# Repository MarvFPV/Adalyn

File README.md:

# Adalyn
36key QAZ-like handwired keyboard based on the great idea by somepin here on GitHub, check out his repo [here](https://github.com/somepin/qal-handwire)

Handwires of the keyboard are confirmed working, although we also have someone working on a PCB. 
Currently, the top and bottom are pretty much a friction fit, be aware of that when printing / ordering this case from a fab.

## Required components for handwires
(For building a handwired Adalyn please use the 3D files from the handwire branch)

* 36 MX style switches
* 2 2u MX platemount stabs
* 36 Diodes
* a Promicro
* one of ai03's [unified daughterboards](https://github.com/ai03-2725/Unified-Daughterboard)
* a few cables to wire up the matrix
* 4 m3x6mm screws
* 4 m3x8mm countersunk screws

I personally tend to remove the microUSB connector from the Promicro and solder it directly to a unified daughterboard, that's also why the Promicro cutout may not fit with the USB connector still on the PCB. (I should really write up some documentation on that ^^)

## PCB version
The adjusted Case files for the PCB version are currently not on this repo, they will be added later down the line.

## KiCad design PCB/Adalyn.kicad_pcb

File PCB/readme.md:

# Adalyn PCB
After the development of the handwired Adalyn case, it was clear this great combination needed a formalized pcb. This is that PCB. Designed by tominabox1, the pcb features an ATmega32u4a, USB-C, and ESD protection. The pcb is supported in QMK and VIAL. 

# BOM
The bill of materials is listed below, with LCSC parts where possible. Total unique part count: 14. Total parts: 37. 

| Ref                                                                                                        | Qnty | Value              | Part     | Footprint                                                          |
|------------------------------------------------------------------------------------------------------------|------|--------------------|----------|--------------------------------------------------------------------|
| C1, C2, C4, C101                                                                                           | 4    | 100nF              | C187860  | 0603                                                               |
| C5                                                                                                         | 1    | 10uF               | C97885   | 0603                                                               |
| C6                                                                                                         | 1    | 1uF                | C302042  | 0603                                                               |
| D101, D102, D103, D104, D105, D106, D107, D108, D109, D110, D111, D112, D113, D114, D115, D116, D117, D118 | 18   | BAV70              | C181110  | SOT-23                                                             |
| F101                                                                                                       | 1    | 700mA              | C182438  | 0603                                                               |
| L101                                                                                                       | 1    | 600R@100MHz        | C139183  | 0603                                                               |
| R2, R3                                                                                                     | 2    | 22                 | C96423   | 0603                                                               |
| R4, R5                                                                                                     | 2    | 10k                | C73809   | 0603                                                               |
| R101, R102                                                                                                 | 2    | 5.1k               | C415096  | 0603                                                               |
| SW1                                                                                                        | 1    | SW_Push            | C589220  | 4.9x4.9                                                            |
| U101                                                                                                       | 1    | ATmega32U4-A       | C44854   | TQFP-44_10x10mm_P0.8mm                                             |
| U102                                                                                                       | 1    | PRTR5V0U2X         | C2827688 | SOT-143                                                            |
| USB101                                                                                                     | 1    | HRO-TYPE-C-31-M-12 | C165948  | HRO-TYPE-C-31-M-12                                                 |
| Y1                                                                                                         | 1    | 16MHz              | C341521  | Crystal:Resonator_SMD_Murata_CSTxExxV-3Pin_3.0x1.1mm_HandSoldering |

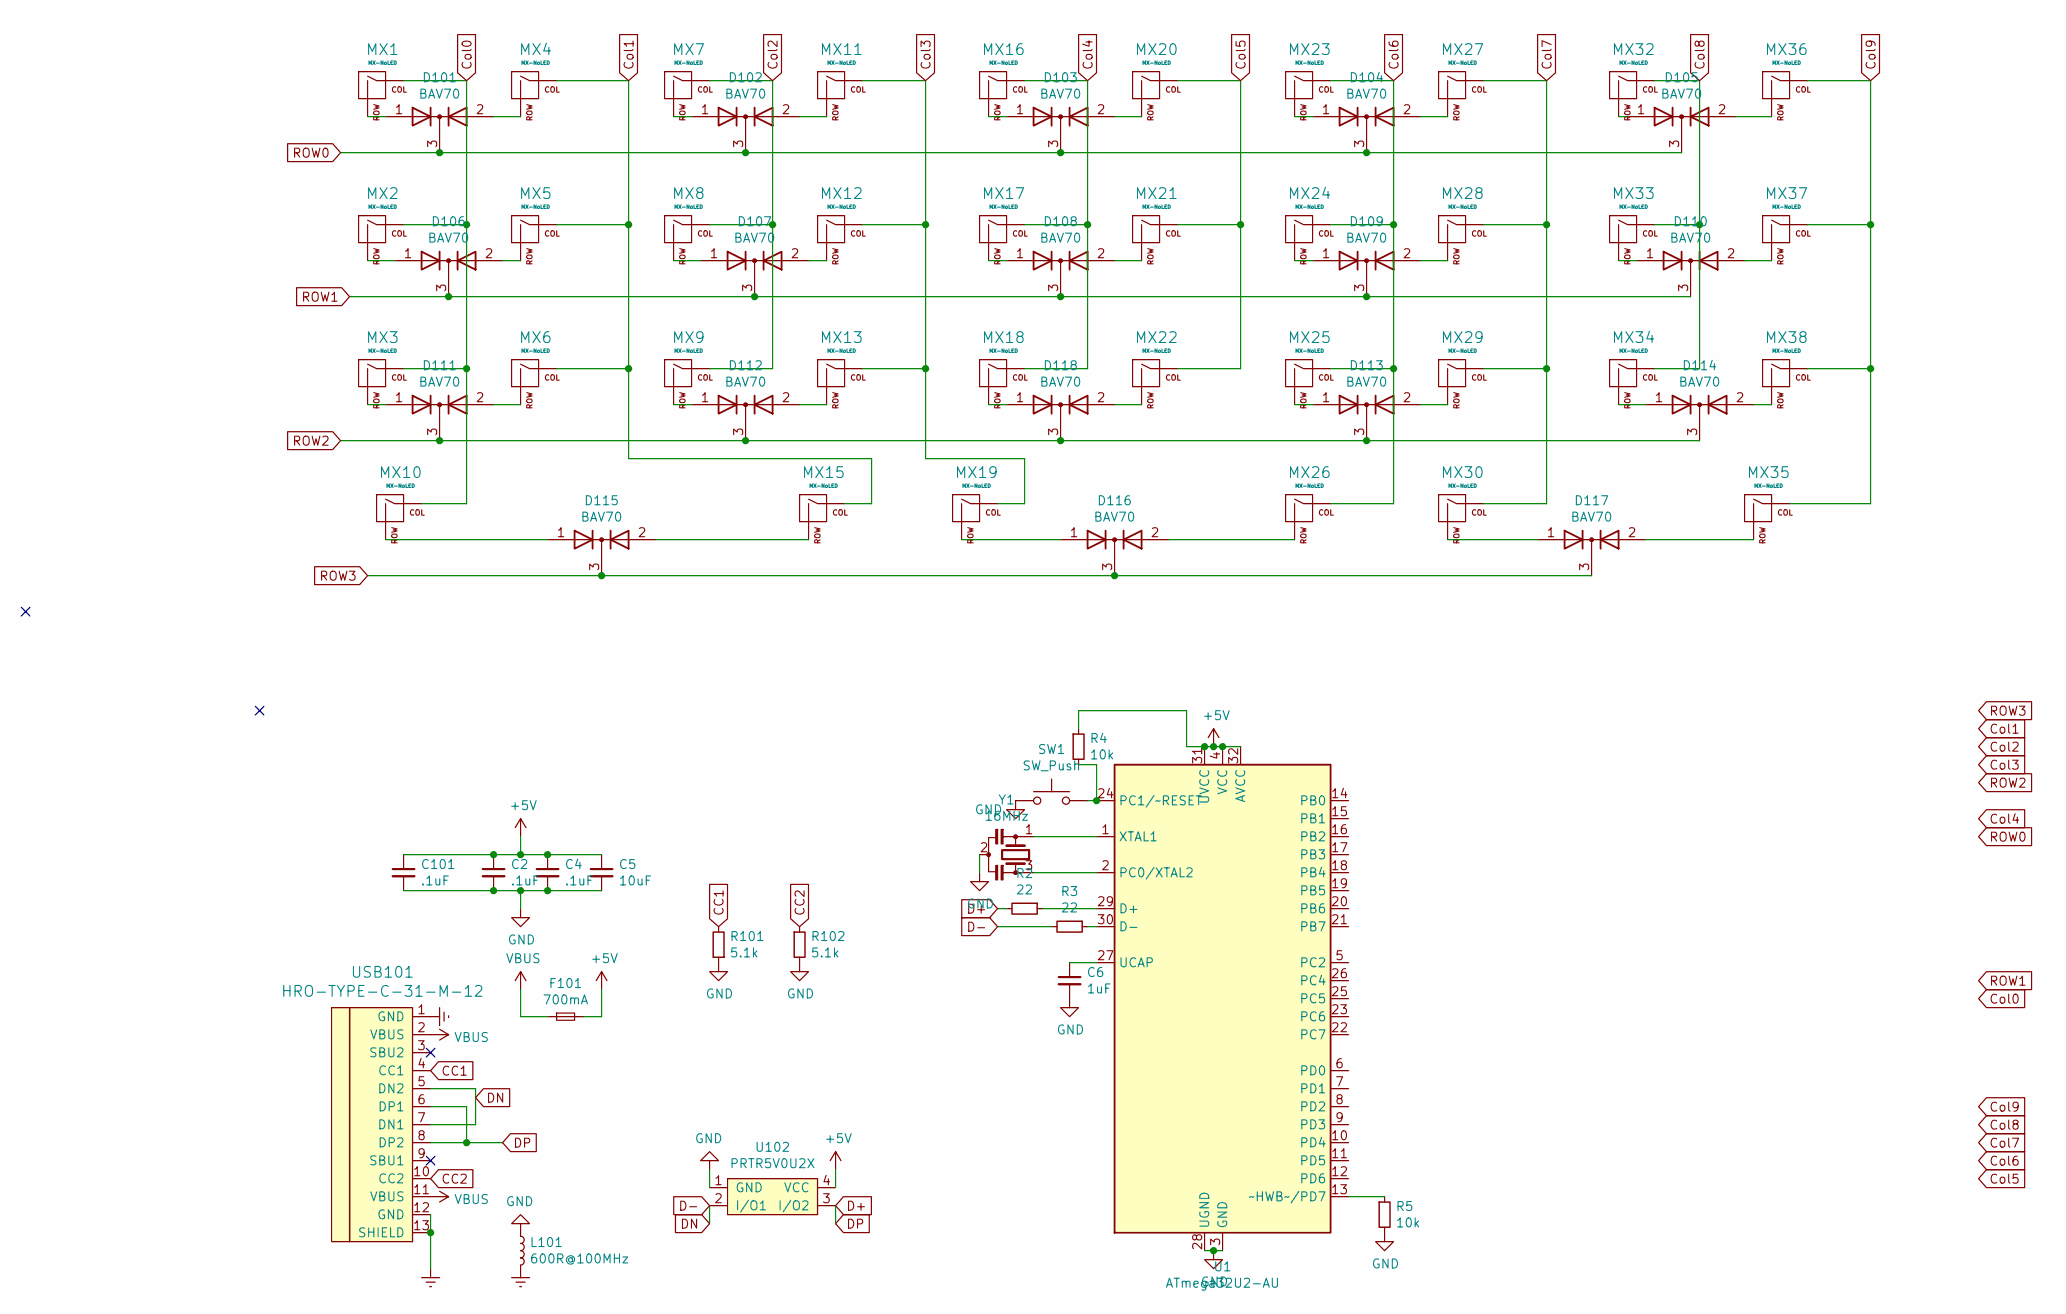
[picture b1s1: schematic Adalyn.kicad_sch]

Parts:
C2, C4, C101: .1uF; C_0603_1608Metric_Pad1.08x0.95mm_HandSolder
C5: 10uF; C_0603_1608Metric_Pad1.08x0.95mm_HandSolder
C6: 1uF; C_0603_1608Metric_Pad1.08x0.95mm_HandSolder
D101, D102, D103, D104, D105, D106, D107, D108, D109, D110, D111, D112, D113, D114, D115, D116, D117, D118: BAV70; SOT-23
F101: 700mA; Fuse_0603_1608Metric
L101: 600R@100MHz; L_0603_1608Metric
MX1, MX2, MX3, MX4, MX5, MX6, MX7, MX8, MX9, MX10, MX11, MX12, MX13, MX15, MX16, MX17, MX18, MX19, MX20, MX21, MX22, MX23, MX24, MX25, MX26, MX27, MX28, MX29, MX30, MX32, MX33, MX34, MX35, MX36, MX37, MX38: MX-NoLED; MXOnly-1U-NoLED
R2, R3: 22; R_0603_1608Metric_Pad0.98x0.95mm_HandSolder
R4, R5: 10k; R_0603_1608Metric_Pad0.98x0.95mm_HandSolder
R101, R102: 5.1k; R_0603_1608Metric
SW1: SW_Push; SW_SPST_TL3342
U1: ATmega32U2-AU; TQFP-32_7x7mm_P0.8mm
U102: PRTR5V0U2X; SOT-143
USB101: HRO-TYPE-C-31-M-12; HRO-TYPE-C-31-M-12-Assembly
Y1: 16MHz; Resonator_SMD_muRata_CSTxExxV-3Pin_3.0x1.1mm

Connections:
+5V: C2.1, C4.1, C5.1, C101.1, F101.2, R4.1, U1.4 (VCC), U1.31 (UVCC), U1.32 (AVCC), U102.4 (VCC)
CC1: R101.2, USB101.4 (CC1)
CC2: R102.1, USB101.10 (CC2)
Col0: MX1.1 (COL), MX2.1 (COL), MX3.1 (COL), MX10.1 (COL)
Col1: MX4.1 (COL), MX5.1 (COL), MX6.1 (COL), MX15.1 (COL)
Col2: MX7.1 (COL), MX8.1 (COL), MX9.1 (COL)
Col3: MX11.1 (COL), MX12.1 (COL), MX13.1 (COL), MX19.1 (COL)
Col4: MX16.1 (COL), MX17.1 (COL), MX18.1 (COL)
Col5: MX20.1 (COL), MX21.1 (COL), MX22.1 (COL)
Col6: MX23.1 (COL), MX24.1 (COL), MX25.1 (COL), MX26.1 (COL)
Col7: MX27.1 (COL), MX28.1 (COL), MX29.1 (COL), MX30.1 (COL)
Col8: MX32.1 (COL), MX33.1 (COL), MX34.1 (COL)
Col9: MX35.1 (COL), MX36.1 (COL), MX37.1 (COL), MX38.1 (COL)
D+: R2.2, U102.3 (I/O2), USB101.6 (DP1), USB101.8 (DP2)
D-: R3.2, U102.2 (I/O1), USB101.5 (DN2), USB101.7 (DN1)
Earth: L101.2, USB101.1 (GND), USB101.12 (GND), USB101.13 (SHIELD)
GND: C2.2, C4.2, C5.2, C6.2, C101.2, L101.1, R5.2, R101.1, R102.2, SW1.1, U1.3 (GND), U1.28 (UGND), U102.1 (GND), Y1.2
unnamed: C6.1, U1.27 (UCAP)
unnamed: D101.1 (A), MX1.2 (ROW)
unnamed: D101.2 (A), MX4.2 (ROW)
unnamed: D102.1 (A), MX7.2 (ROW)
unnamed: D102.2 (A), MX11.2 (ROW)
unnamed: D103.1 (A), MX16.2 (ROW)
unnamed: D103.2 (A), MX20.2 (ROW)
unnamed: D104.1 (A), MX23.2 (ROW)
unnamed: D104.2 (A), MX27.2 (ROW)
unnamed: D105.1 (A), MX32.2 (ROW)
unnamed: D105.2 (A), MX36.2 (ROW)
unnamed: D106.1 (A), MX2.2 (ROW)
unnamed: D106.2 (A), MX5.2 (ROW)
unnamed: D107.1 (A), MX8.2 (ROW)
unnamed: D107.2 (A), MX12.2 (ROW)
unnamed: D108.1 (A), MX17.2 (ROW)
unnamed: D108.2 (A), MX21.2 (ROW)
unnamed: D109.1 (A), MX24.2 (ROW)
unnamed: D109.2 (A), MX28.2 (ROW)
unnamed: D110.1 (A), MX33.2 (ROW)
unnamed: D110.2 (A), MX37.2 (ROW)
unnamed: D111.1 (A), MX3.2 (ROW)
unnamed: D111.2 (A), MX6.2 (ROW)
unnamed: D112.1 (A), MX9.2 (ROW)
unnamed: D112.2 (A), MX13.2 (ROW)
unnamed: D113.1 (A), MX25.2 (ROW)
unnamed: D113.2 (A), MX29.2 (ROW)
unnamed: D114.1 (A), MX34.2 (ROW)
unnamed: D114.2 (A), MX38.2 (ROW)
unnamed: D115.1 (A), MX10.2 (ROW)
unnamed: D115.2 (A), MX15.2 (ROW)
unnamed: D116.1 (A), MX19.2 (ROW)
unnamed: D116.2 (A), MX26.2 (ROW)
unnamed: D117.1 (A), MX30.2 (ROW)
unnamed: D117.2 (A), MX35.2 (ROW)
unnamed: D118.1 (A), MX18.2 (ROW)
unnamed: D118.2 (A), MX22.2 (ROW)
unnamed: R2.1, U1.29 (D+)
unnamed: R3.1, U1.30 (D-)
unnamed: R4.2, SW1.2, U1.24 (PC1/~RESET)
unnamed: R5.1, U1.13 (~HWB~/PD7)
unnamed: U1.1 (XTAL1), Y1.1
unnamed: U1.2 (PC0/XTAL2), Y1.3
ROW0: D101.3 (K), D102.3 (K), D103.3 (K), D104.3 (K), D105.3 (K)
ROW1: D106.3 (K), D107.3 (K), D108.3 (K), D109.3 (K), D110.3 (K)
ROW2: D111.3 (K), D112.3 (K), D113.3 (K), D114.3 (K), D118.3 (K)
ROW3: D115.3 (K), D116.3 (K), D117.3 (K)
VBUS: F101.1, USB101.2 (VBUS), USB101.11 (VBUS)

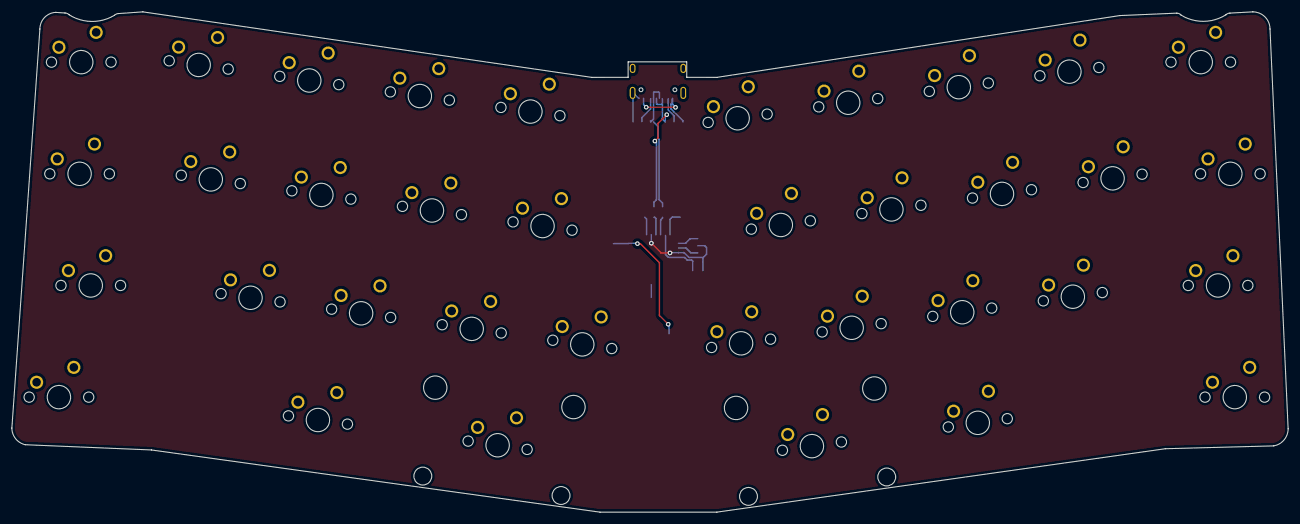
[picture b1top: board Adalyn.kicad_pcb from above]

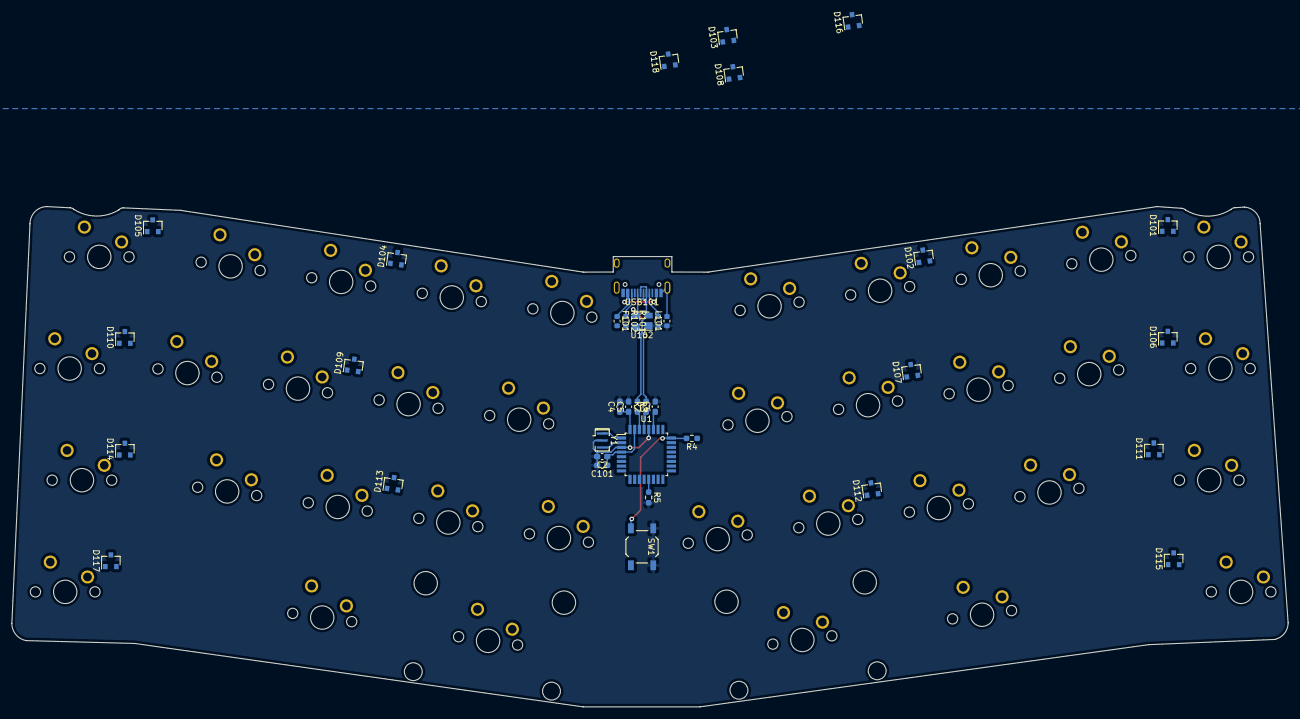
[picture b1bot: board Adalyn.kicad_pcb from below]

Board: 2 copper layers, 217.7 x 85.3 mm, 72 parts (36 on the bottom side), 65 nets.

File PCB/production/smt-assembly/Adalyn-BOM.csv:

Comment,Designator,Footprint,LCSC
".1uF","C2,C4,C101","Capacitor_SMD:C_0805_2012Metric","C49678"
"10uF","C5","Capacitor_SMD:C_0805_2012Metric","C91245"
"1uF","C6","Capacitor_SMD:C_0805_2012Metric","C28323"
"22pf","C7,C8","Capacitor_SMD:C_0805_2012Metric","C1804"
"BAV70","D101,D102,D103,D104,D105,D106,D107,D108,D109,D110,D111,D112,D113,D114,D115,D116,D117,D118","Package_TO_SOT_SMD:SOT-23","C68978"
"Polyfuse","F101","Fuse:Fuse_1206_3216Metric","C69688"
"600R@100MHz","L101","Inductor_SMD:L_0603_1608Metric",""
"MX-NoLED","MX1,MX2,MX3,MX4,MX5,MX6,MX7,MX8,MX9,MX10,MX11,MX12,MX13,MX15,MX16,MX17,MX18,MX19,MX20,MX21,MX22,MX23,MX24,MX25,MX26,MX27,MX28,MX29,MX30,MX32,MX33,MX34,MX35,MX36,MX37,MX38","marbastlib-mx:SW_MX_1u",""
"5.1k","R101,R102","Resistor_SMD:R_0805_2012Metric","C27834"
"22","R2,R3","Resistor_SMD:R_0805_2012Metric","C17561"
"10k","R4,R5","Resistor_SMD:R_0805_2012Metric","C17414"
"SW_Push","SW1","Keebio-Parts:SW_SPST_TL3342","C318884"
"ATmega32U2-AU","U1","Package_QFP:TQFP-32_7x7mm_P0.8mm","C618733"
"SRV05-4","U102","Package_TO_SOT_SMD:SOT-23-6",""
"HRO-TYPE-C-31-M-12","USB101","Type-C:HRO-TYPE-C-31-M-12-Assembly","C165948"
"Crystal_GND24_Small","Y1","Crystal:Crystal_SMD_3225-4Pin_3.2x2.5mm","C13738"

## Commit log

2021-07-07 v0.1 upload
2021-07-08 i am smart
2021-08-19 Create LICENSE
2021-08-29 added pcb version
2021-11-18 Inital commit of PCB stuff
2021-11-22 NOT FINSIHED, first commit
2022-01-15 puuuush
2022-01-16 initial commit: updated bom,pos, finished routing
2022-01-17 updated silkscreen and gerber files
2022-01-18 updated silkscreen
2022-01-18 finalized board, added updated gerber / bom/pos
2022-01-18 cleared silkscreen, updated README
